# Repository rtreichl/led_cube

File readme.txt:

TODOs and Thoughts

switch programm {
case 0:
	programm += cube_rot(&index, &cube, ....);
	break;
case 1:
	programm += cube_shift(&index, &cube, ....);
	break;
........
};

Selfshifting architecture!!! (see above)
Try to make a cmake project!!
All configurations should be included in one file!!
Use Doxigen write-style for comments (very important! will be used for generate a automatically documentation)
Use C-programmes instead of model-data-structure. (Not enough Space avalible!!!)
Try to use BT-connection for a PC-controled mode!!! (messaure time delay between PC <-> µC)
Programm rotated output, this means move base which is bottom to left, right, front, back and top!!!
Output functions can be controlled from animation functions, this means output functions were called over function pointer,
which were set from animations function.
All output, animation functions must have the same Parameterlist, use void pointer to access them with different data!
Try to implement a section programing interface instead of a pagewise one!
Bootloader should have a login interface too!
Optimize BT-Interface for terminal. (Maybe Login & Pwd Login)
Write a Android app for controll the actually shown programm.(programm = bt_android_code(....))
Reprogramm global time base can be accessed from any part in programm but should be not global use pointer!!!
PC-programm has to be included a serial-interface (requires a bluetooth driver that includes a serial to bluetooth interface)
Usefull options for PC-programm could be a compile option + including the resulting object file to simulate!!! (Not sure if this would work)
Move GIT repository from Cloudforge to Github.(Done!)
Maybe try to make a second version of board which includes a Cortex-M0 µC or something like this.(Problem is requires a new Programmer!)
Redesinge some layout faults from first version of board (new placement of pinheader, change all voltage regulators, ....)

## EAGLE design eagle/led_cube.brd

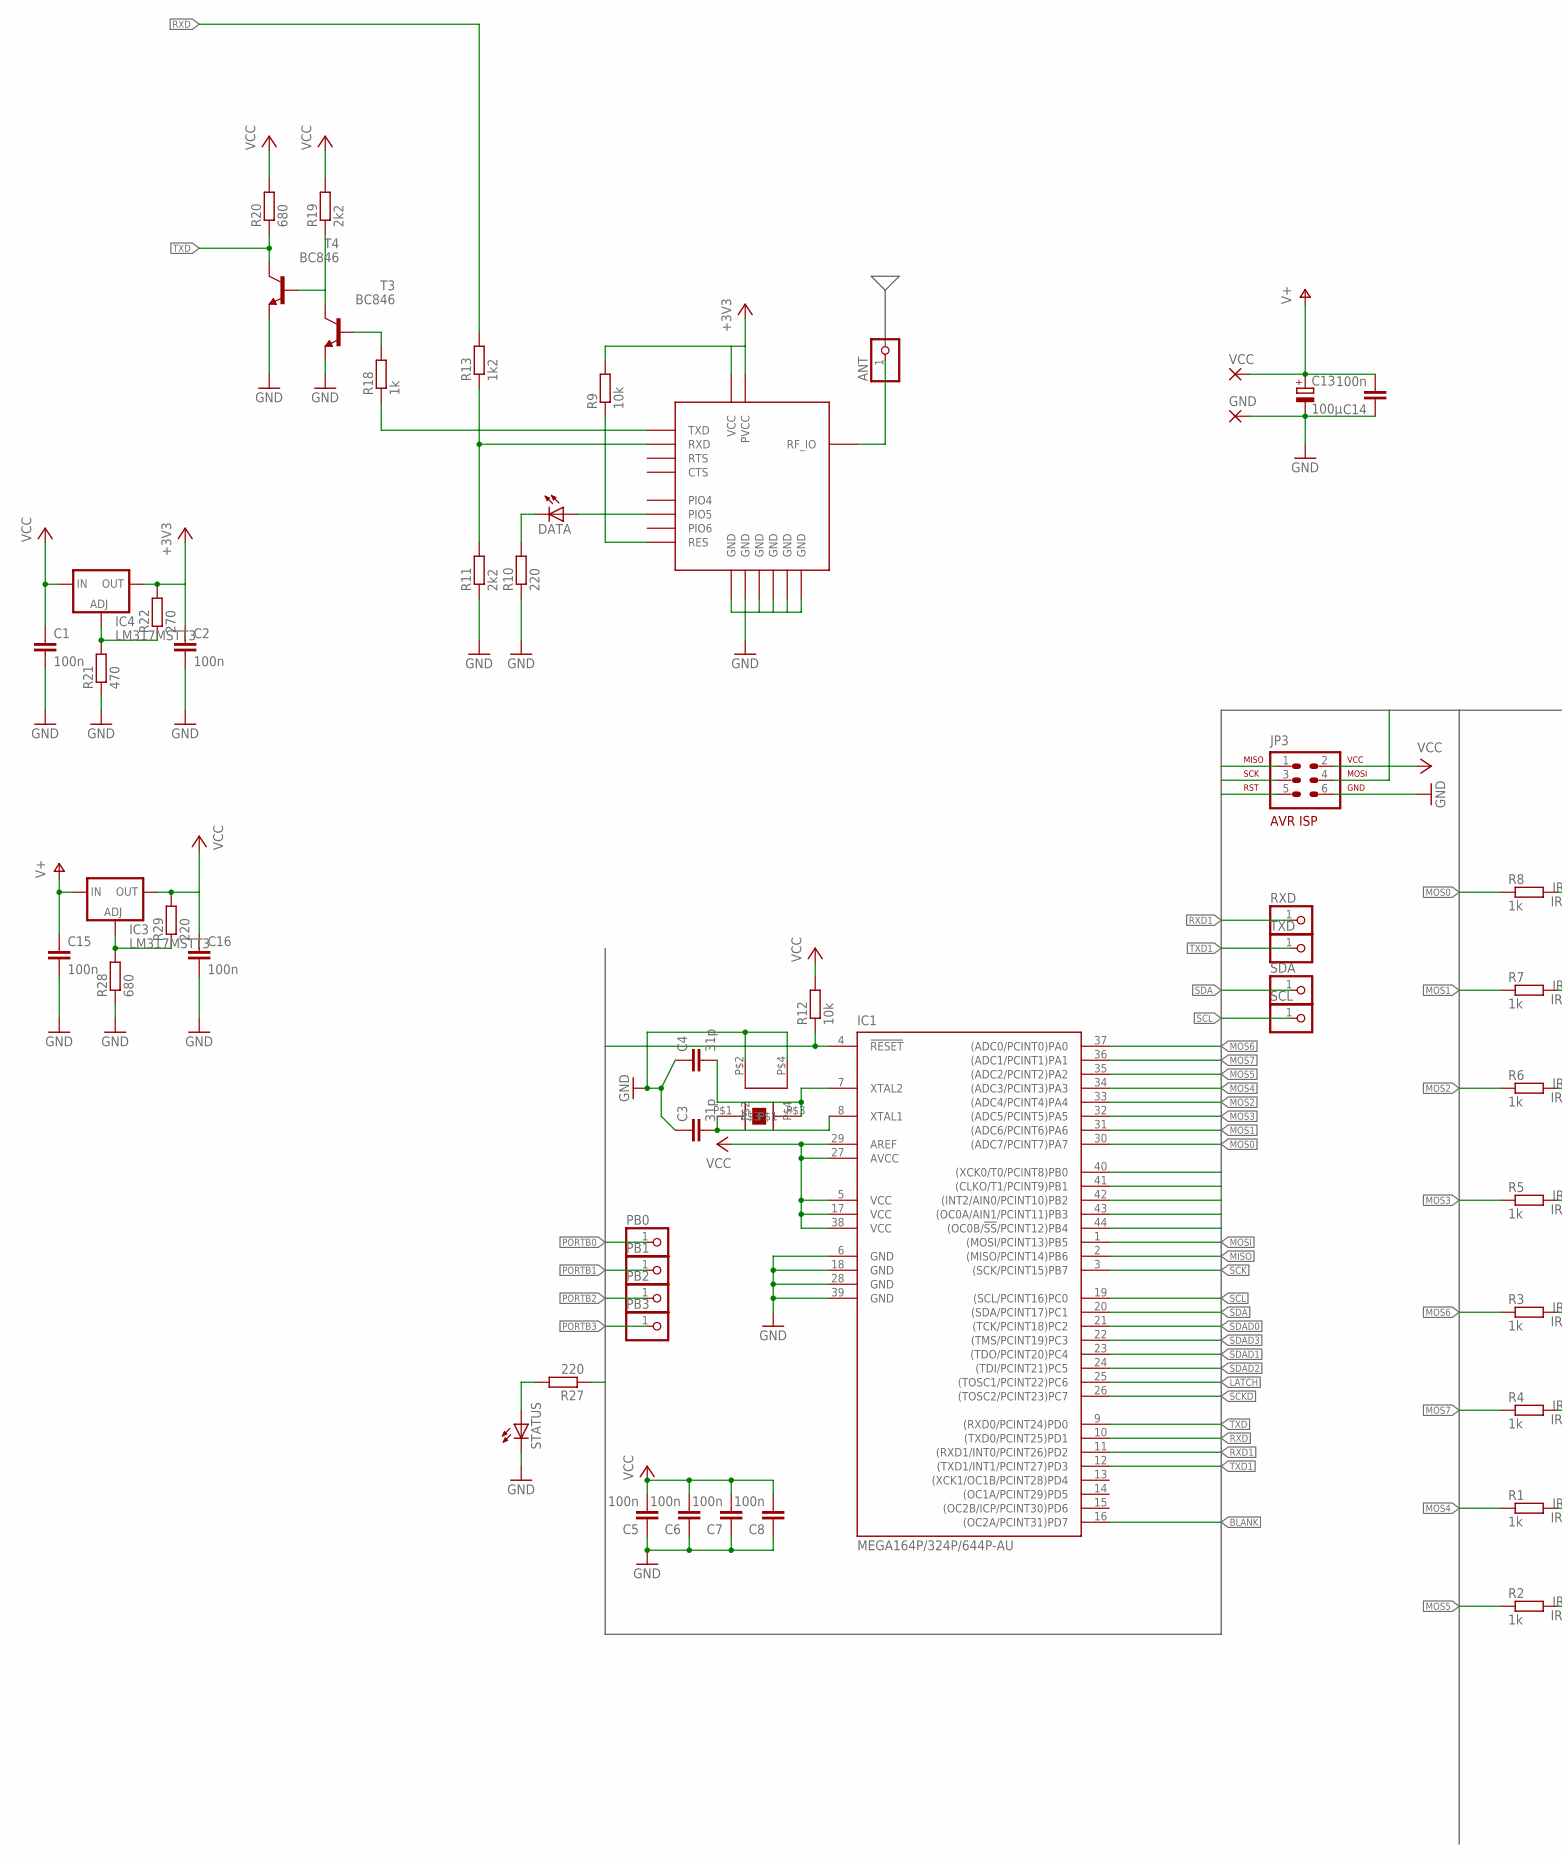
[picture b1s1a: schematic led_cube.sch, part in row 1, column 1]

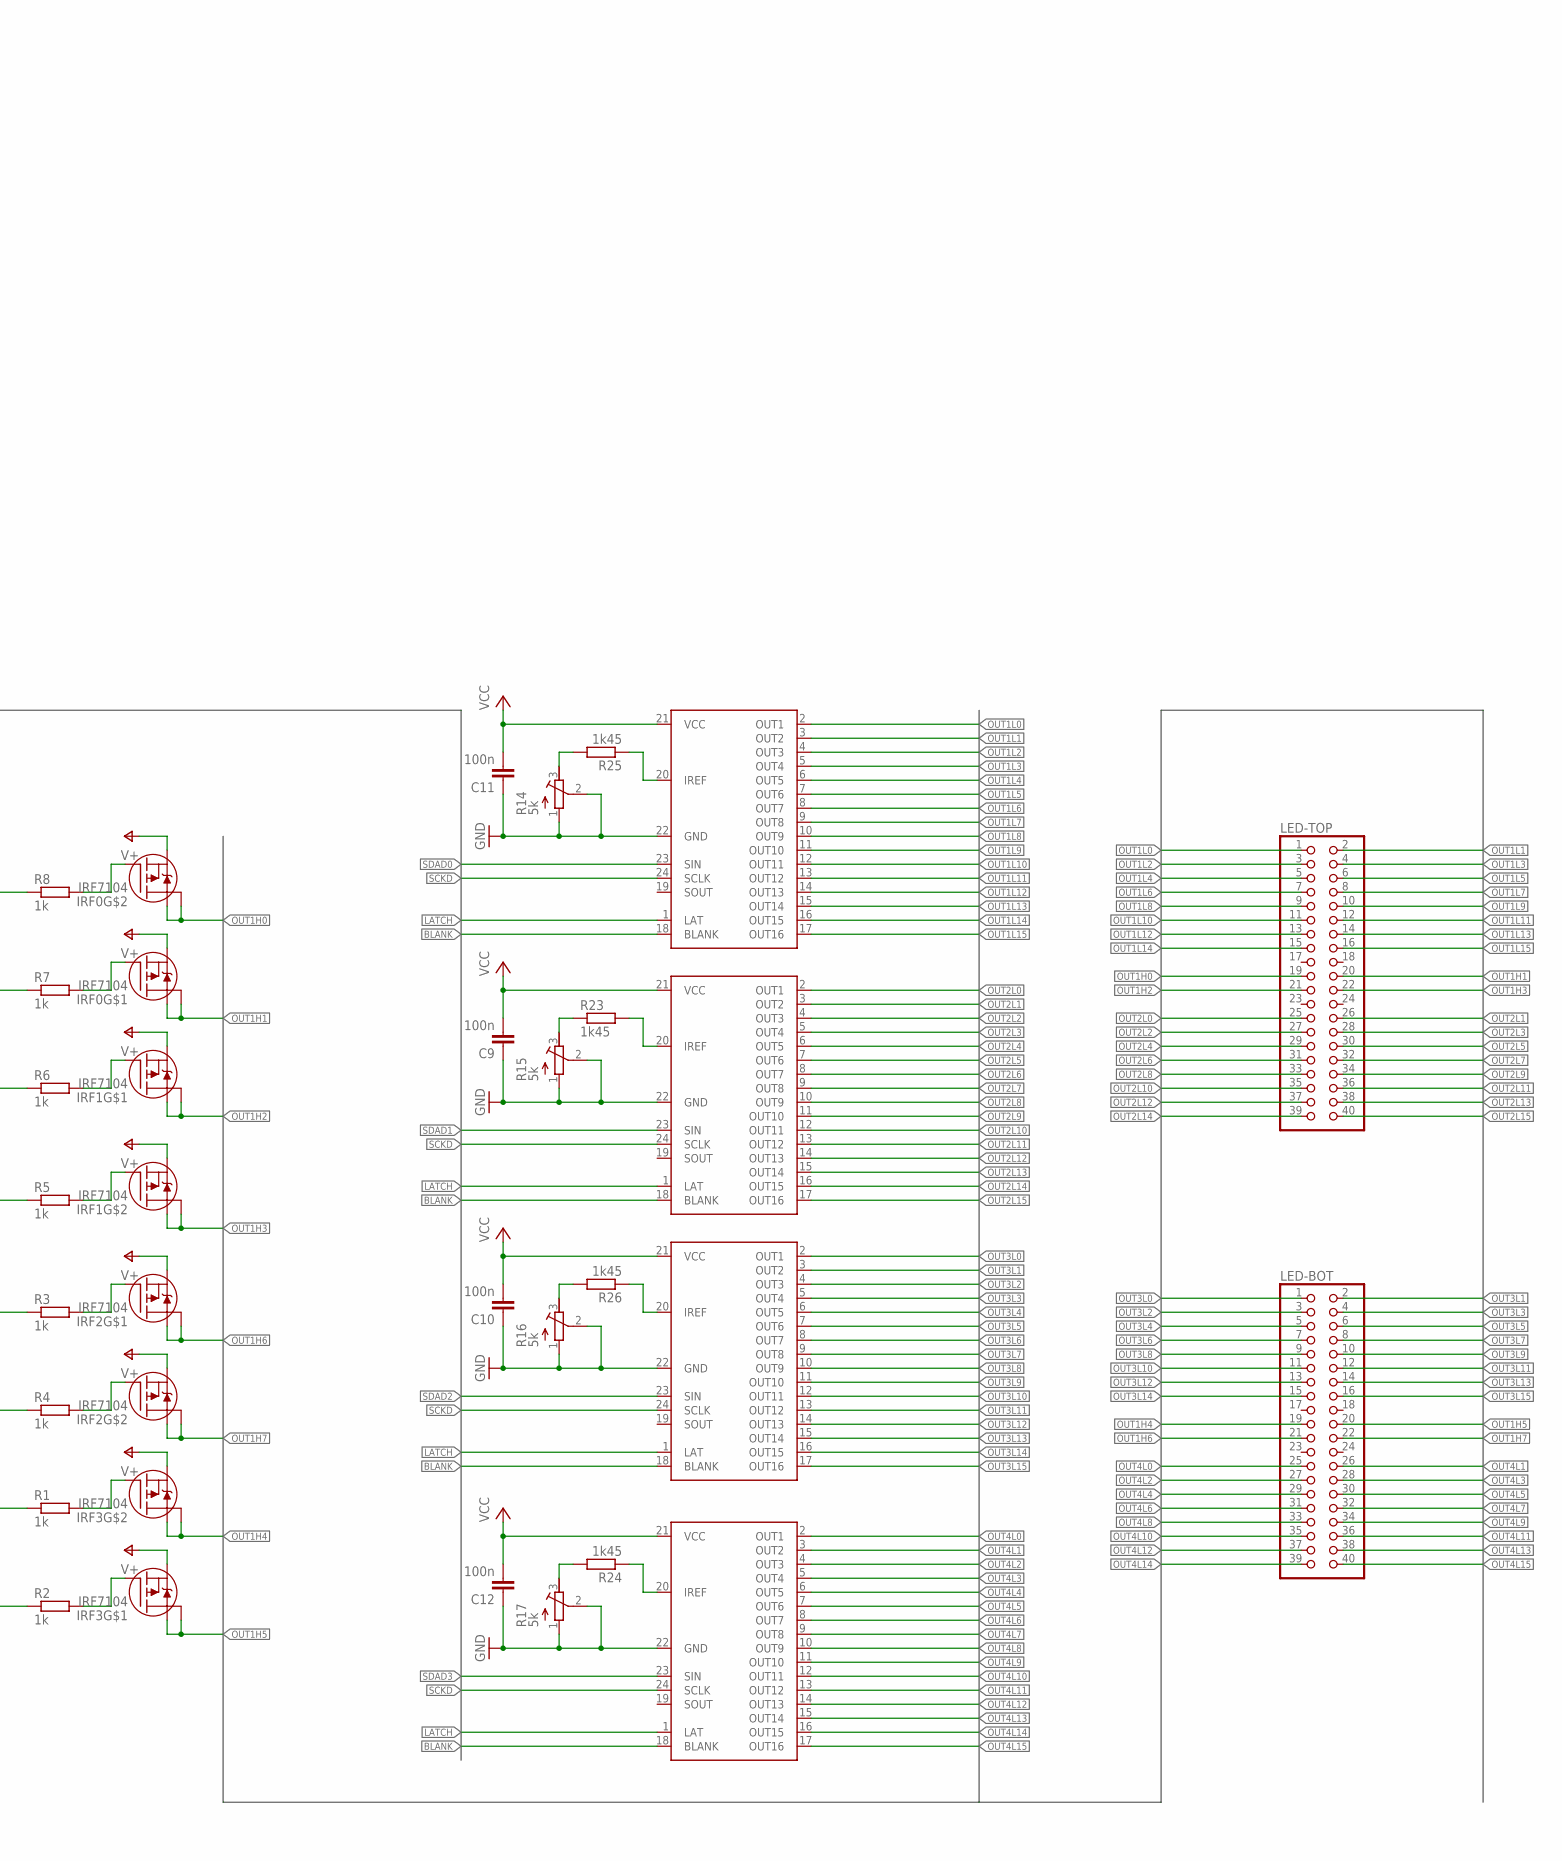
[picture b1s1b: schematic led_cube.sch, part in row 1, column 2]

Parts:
ANT: PINHD-1X1; 1X01
C1, C2, C5, C6, C7, C8, C9, C10, C11, C12, C14, C15, C16: 100n; C0805
C3, C4: 31p; C0805
C13: 100µ; PANASONIC_D
DATA: LEDCHIPLED_1206; CHIPLED_1206
GND: 2,54/1,0
IC1: MEGA164P/324P/644P-AU; TQFP44
IC2: BTM_SER; BTM_222
IC3, IC4: LM317MSTT3; SOT223
IRF0, IRF1, IRF2, IRF3: IRF7104; SO8-2
JP3: AVR-ISP-6VERT; AVR-ISP-6
LED-BOT: PINHD-2X20; 2X20
LED-TOP: PINHD-2X20; 2X20
PB0, PB1, PB2, PB3: PINHD-1X1; 1X01
R1, R2, R3, R4, R5, R6, R7, R8, R18: 1k; R0805
R9, R12: 10k; R0805
R10, R27, R29: 220; R0805
R11, R19: 2k2; R0805
R13: 1k2; R0805
R14, R15, R16, R17: 5k; RTRIM3202
R20, R28: 680; R0805
R21: 470; R0805
R22: 270; R0805
R23, R24, R25, R26: 1k45; R0805
RXD: PINHD-1X1; 1X01
SCL: PINHD-1X1; 1X01
SDA: PINHD-1X1; 1X01
STATUS: LEDCHIPLED_1206; CHIPLED_1206
T3, T4: BC846; SOT23
TLC0, TLC1, TLC2, TLC3: TLC5929RGE; HVQFN24
TXD: PINHD-1X1; 1X01
U$9: ABMM2
VCC: 2,54/1,0

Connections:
+3V3: C2.1, IC2.P$2 (PVCC), IC2.P$17 (VCC), IC4.4 (OUT), R9.2, R22.2
BLANK: IC1.16 ((OC2A/PCINT31)PD7), TLC0.18 (BLANK), TLC1.18 (BLANK), TLC2.18 (BLANK), TLC3.18 (BLANK)
GND: C1.2, C2.2, C3.1, C4.1, C5.1, C6.1, C7.1, C8.1, C9.1, C10.1, C11.1, C12.1, C13.-, C14.1, C15.2, C16.2, GND.1, IC1.6 (GND), IC1.18 (GND), IC1.28 (GND), IC1.39 (GND), IC2.P$1 (GND), IC2.P$10 (GND), IC2.P$18 (GND), IC2.P$19 (GND), IC2.P$29 (GND), IC2.P$38 (GND), JP3.6, R10.1, R11.1, R14.1 (A), R14.2 (S), R15.1 (A), R15.2 (S), R16.1 (A), R16.2 (S), R17.1 (A), R17.2 (S), R21.1, R28.1, STATUS.C, T3.2 (E), T4.2 (E), TLC0.22 (GND), TLC1.22 (GND), TLC2.22 (GND), TLC3.22 (GND), U$9.P$2, U$9.P$4
LATCH: IC1.25 ((TOSC1/PCINT22)PC6), TLC0.1 (LAT), TLC1.1 (LAT), TLC2.1 (LAT), TLC3.1 (LAT)
MISO: IC1.2 ((MISO/PCINT14)PB6), JP3.1
MOS0: IC1.30 ((ADC7/PCINT7)PA7), R8.1
MOS1: IC1.31 ((ADC6/PCINT6)PA6), R7.1
MOS2: IC1.33 ((ADC4/PCINT4)PA4), R6.1
MOS3: IC1.32 ((ADC5/PCINT5)PA5), R5.1
MOS4: IC1.34 ((ADC3/PCINT3)PA3), R1.1
MOS5: IC1.35 ((ADC2/PCINT2)PA2), R2.1
MOS6: IC1.37 ((ADC0/PCINT0)PA0), R3.1
MOS7: IC1.36 ((ADC1/PCINT1)PA1), R4.1
MOSI: IC1.1 ((MOSI/PCINT13)PB5), JP3.4
unnamed: C3.2, IC1.8 (XTAL1), U$9.P$1
unnamed: IC2.P$26 (RXD), R11.2, R13.1
unnamed: C4.2, IC1.7 (XTAL2), U$9.P$3
unnamed: IRF3.2 (G), R2.2
unnamed: IC2.P$16 (RES), R9.1
unnamed: DATA.A, IC2.P$11 (PIO5)
unnamed: DATA.C, R10.2
unnamed: IRF3.4 (G), R1.2
unnamed: IRF2.4 (G), R4.2
unnamed: IC2.P$27 (TXD), R18.1
unnamed: R18.2, T3.1 (B)
unnamed: R19.1, T3.3 (C), T4.1 (B)
unnamed: IRF2.2 (G), R3.2
unnamed: IC4.1 (ADJ), R21.2, R22.1
unnamed: IRF1.4 (G), R5.2
unnamed: IRF1.2 (G), R6.2
unnamed: IRF0.2 (G), R7.2
unnamed: IRF0.4 (G), R8.2
unnamed: R24.1, TLC3.20 (IREF)
unnamed: R17.3 (E), R24.2
unnamed: R16.3 (E), R26.2
unnamed: R26.1, TLC2.20 (IREF)
unnamed: R23.2, TLC1.20 (IREF)
unnamed: R15.3 (E), R23.1
unnamed: R14.3 (E), R25.2
unnamed: R25.1, TLC0.20 (IREF)
unnamed: ANT.1, IC2.P$37 (RF_IO)
unnamed: R27.2, STATUS.A
unnamed: IC3.1 (ADJ), R28.2, R29.1
OUT1H0: IRF0.5 (D), IRF0.6 (D), LED-TOP.19
OUT1H1: IRF0.7 (D), IRF0.8 (D), LED-TOP.20
OUT1H2: IRF1.7 (D), IRF1.8 (D), LED-TOP.21
OUT1H3: IRF1.5 (D), IRF1.6 (D), LED-TOP.22
OUT1H4: IRF3.5 (D), IRF3.6 (D), LED-BOT.19
OUT1H5: IRF3.7 (D), IRF3.8 (D), LED-BOT.20
OUT1H6: IRF2.7 (D), IRF2.8 (D), LED-BOT.21
OUT1H7: IRF2.5 (D), IRF2.6 (D), LED-BOT.22
OUT1L0: LED-TOP.1, TLC0.2 (OUT1)
OUT1L1: LED-TOP.2, TLC0.3 (OUT2)
OUT1L2: LED-TOP.3, TLC0.4 (OUT3)
OUT1L3: LED-TOP.4, TLC0.5 (OUT4)
OUT1L4: LED-TOP.5, TLC0.6 (OUT5)
OUT1L5: LED-TOP.6, TLC0.7 (OUT6)
OUT1L6: LED-TOP.7, TLC0.8 (OUT7)
OUT1L7: LED-TOP.8, TLC0.9 (OUT8)
OUT1L8: LED-TOP.9, TLC0.10 (OUT9)
OUT1L9: LED-TOP.10, TLC0.11 (OUT10)
OUT1L10: LED-TOP.11, TLC0.12 (OUT11)
OUT1L11: LED-TOP.12, TLC0.13 (OUT12)
OUT1L12: LED-TOP.13, TLC0.14 (OUT13)
OUT1L13: LED-TOP.14, TLC0.15 (OUT14)
OUT1L14: LED-TOP.15, TLC0.16 (OUT15)
OUT1L15: LED-TOP.16, TLC0.17 (OUT16)
OUT2L0: LED-TOP.25, TLC1.2 (OUT1)
OUT2L1: LED-TOP.26, TLC1.3 (OUT2)
OUT2L2: LED-TOP.27, TLC1.4 (OUT3)
OUT2L3: LED-TOP.28, TLC1.5 (OUT4)
OUT2L4: LED-TOP.29, TLC1.6 (OUT5)
OUT2L5: LED-TOP.30, TLC1.7 (OUT6)
OUT2L6: LED-TOP.31, TLC1.8 (OUT7)
OUT2L7: LED-TOP.32, TLC1.9 (OUT8)
OUT2L8: LED-TOP.33, TLC1.10 (OUT9)
OUT2L9: LED-TOP.34, TLC1.11 (OUT10)
OUT2L10: LED-TOP.35, TLC1.12 (OUT11)
OUT2L11: LED-TOP.36, TLC1.13 (OUT12)
OUT2L12: LED-TOP.37, TLC1.14 (OUT13)
OUT2L13: LED-TOP.38, TLC1.15 (OUT14)
OUT2L14: LED-TOP.39, TLC1.16 (OUT15)
OUT2L15: LED-TOP.40, TLC1.17 (OUT16)
OUT3L0: LED-BOT.1, TLC2.2 (OUT1)
OUT3L1: LED-BOT.2, TLC2.3 (OUT2)
OUT3L2: LED-BOT.3, TLC2.4 (OUT3)
OUT3L3: LED-BOT.4, TLC2.5 (OUT4)
OUT3L4: LED-BOT.5, TLC2.6 (OUT5)
OUT3L5: LED-BOT.6, TLC2.7 (OUT6)
OUT3L6: LED-BOT.7, TLC2.8 (OUT7)
OUT3L7: LED-BOT.8, TLC2.9 (OUT8)
OUT3L8: LED-BOT.9, TLC2.10 (OUT9)
OUT3L9: LED-BOT.10, TLC2.11 (OUT10)
OUT3L10: LED-BOT.11, TLC2.12 (OUT11)
OUT3L11: LED-BOT.12, TLC2.13 (OUT12)
OUT3L12: LED-BOT.13, TLC2.14 (OUT13)
OUT3L13: LED-BOT.14, TLC2.15 (OUT14)
OUT3L14: LED-BOT.15, TLC2.16 (OUT15)
OUT3L15: LED-BOT.16, TLC2.17 (OUT16)
OUT4L0: LED-BOT.25, TLC3.2 (OUT1)
OUT4L1: LED-BOT.26, TLC3.3 (OUT2)
OUT4L2: LED-BOT.27, TLC3.4 (OUT3)
OUT4L3: LED-BOT.28, TLC3.5 (OUT4)
OUT4L4: LED-BOT.29, TLC3.6 (OUT5)
OUT4L5: LED-BOT.30, TLC3.7 (OUT6)
OUT4L6: LED-BOT.31, TLC3.8 (OUT7)
OUT4L7: LED-BOT.32, TLC3.9 (OUT8)
OUT4L8: LED-BOT.33, TLC3.10 (OUT9)
OUT4L9: LED-BOT.34, TLC3.11 (OUT10)
OUT4L10: LED-BOT.35, TLC3.12 (OUT11)
OUT4L11: LED-BOT.36, TLC3.13 (OUT12)
OUT4L12: LED-BOT.37, TLC3.14 (OUT13)
OUT4L13: LED-BOT.38, TLC3.15 (OUT14)
OUT4L14: LED-BOT.39, TLC3.16 (OUT15)
OUT4L15: LED-BOT.40, TLC3.17 (OUT16)
PORTB0: IC1.40 ((XCK0/T0/PCINT8)PB0), PB0.1
PORTB1: IC1.41 ((CLKO/T1/PCINT9)PB1), PB1.1
PORTB2: IC1.42 ((INT2/AIN0/PCINT10)PB2), PB2.1
PORTB3: IC1.43 ((OC0A/AIN1/PCINT11)PB3), PB3.1
PORTB4: IC1.44 ((OC0B/!SS!/PCINT12)PB4), R27.1
RST: IC1.4 (!RESET), JP3.5, R12.1
RXD: IC1.10 ((TXD0/PCINT25)PD1), R13.2
RXD1: IC1.11 ((RXD1/INT0/PCINT26)PD2), RXD.1
SCK: IC1.3 ((SCK/PCINT15)PB7), JP3.3
SCKD: IC1.26 ((TOSC2/PCINT23)PC7), TLC0.24 (SCLK), TLC1.24 (SCLK), TLC2.24 (SCLK), TLC3.24 (SCLK)
SCL: IC1.19 ((SCL/PCINT16)PC0), SCL.1
SDA: IC1.20 ((SDA/PCINT17)PC1), SDA.1
SDAD0: IC1.21 ((TCK/PCINT18)PC2), TLC0.23 (SIN)
SDAD1: IC1.23 ((TDO/PCINT20)PC4), TLC1.23 (SIN)
SDAD2: IC1.24 ((TDI/PCINT21)PC5), TLC2.23 (SIN)
SDAD3: IC1.22 ((TMS/PCINT19)PC3), TLC3.23 (SIN)
TXD: IC1.9 ((RXD0/PCINT24)PD0), R20.1, T4.3 (C)
TXD1: IC1.12 ((TXD1/INT1/PCINT27)PD3), TXD.1
V+: C13.+, C14.2, C15.1, IC3.3 (IN), IRF0.1 (S), IRF0.3 (S), IRF1.1 (S), IRF1.3 (S), IRF2.1 (S), IRF2.3 (S), IRF3.1 (S), IRF3.3 (S), VCC.1
VCC: C1.1, C5.2, C6.2, C7.2, C8.2, C9.2, C10.2, C11.2, C12.2, C16.1, IC1.5 (VCC), IC1.17 (VCC), IC1.27 (AVCC), IC1.29 (AREF), IC1.38 (VCC), IC3.4 (OUT), IC4.3 (IN), JP3.2, R12.2, R19.2, R20.2, R29.2, TLC0.21 (VCC), TLC1.21 (VCC), TLC2.21 (VCC), TLC3.21 (VCC)

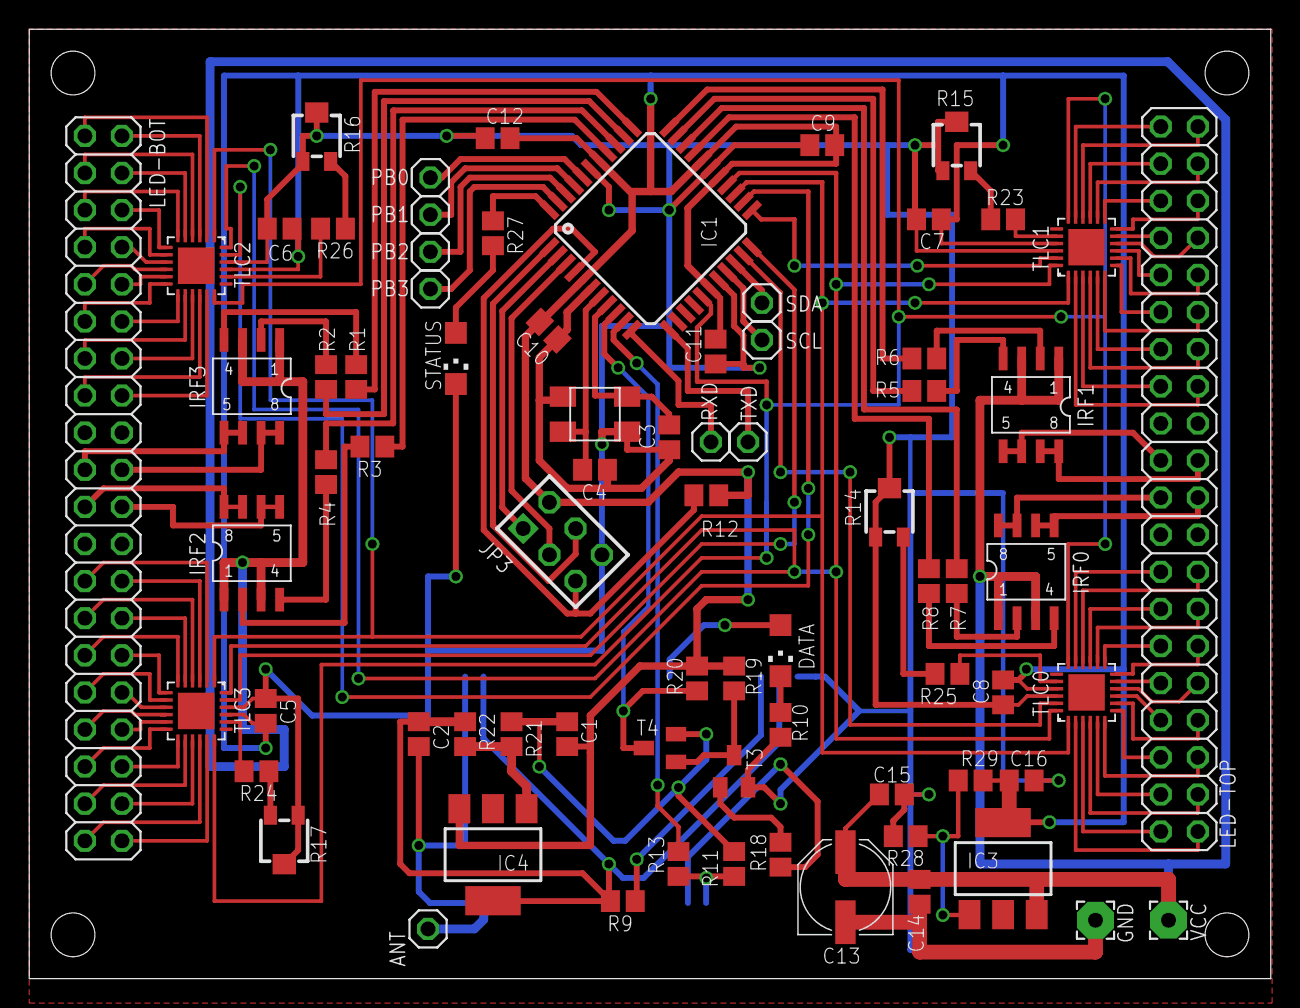
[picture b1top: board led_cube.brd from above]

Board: 2 copper layers, 85.0 x 65.0 mm, 76 parts (1 on the bottom side), 135 nets.

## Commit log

2014-07-23 initialisation
2014-07-23 add: avr folder and files
    Initialisation commit from the old repo.
2014-07-23 add: eagle folder and files
    Initialisation commit from eagle files from old repo.
2014-07-28 chg: reworked output from static to dynamic data.
    deleted data section
    add animation file
    adapted tlc for dynamic
2014-07-31 add: some thoughts for Project
2014-08-03 Lifting
    Did vertical lift up and down.
2014-08-04 backfrontwards
2014-08-04 all axes shifts with small cube
    works
2014-08-04 small simple programm
2014-08-04 intro
    3 - 2 - 1 - GO!
2014-08-04 add: some modles
2014-08-04 chg: added an output from top side
2014-08-04 add: controlflow
2014-08-04 chg: added interface for upcoming content flow
2014-08-04 chg: function pointer array for program execution
    Added function pointer array for execution of the animations. An ending
    program returns 1 which will be added to the ruuning counter. Max
    counter goes to Array limit then start again at zero.
2014-08-04 chg: complete implemtation of animation
2014-08-05 chg: improved implemtation of animation
    moved definition for function pointer from main file to animation file.
    added a new function for flow control (top value is where animation is
    completed, chang value is where tmp counting is changed from postive to
    negative)
2014-08-06 add: sine wave animations
    added a sine wave array from [1 - 10].
    gernerate two different wave forms.
2014-08-13 tmp: asscii tmp commit
2014-08-16 fix: animation didn't stuck at a new char
2014-08-18 add: android app base files.
2014-08-26 Zeug von Ralf
2014-09-02 add: line folower
2014-09-30 chg: animation interface and different things
2014-09-30 add: fine state maschine for pc and matlab interface
2014-09-30 add: windows files for communiction via Bluetooth over serial interface
2014-10-01 chg: serval things
2014-10-01 chg: gitignore
2014-10-01 add: init commit for branch
2015-09-28 INIT: init commit qt programm

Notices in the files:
parts and their libraries:
irf-2: Copyright & License
This library is licensed under the General Public License, Version 2.
More Information about the General Public License is available at http://www.gnu.org/copyleft/gpl.html.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
